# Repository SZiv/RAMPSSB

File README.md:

# RAMPSSB
=== Be sure to take a look at the Wiki before attempting a build: http://reprap.org/wiki/RAMPSSB and if you are curious more as to the development and technological reasoning behind this project, take a look at my blog post at http://scottziv.com/rampssb-bringing-closed-loop-dc-motor-control-to-3d-printers/ ===

RAMPS Servo Board. Released under GPLv3.

Replaces the X and Y stepper drivers on a RAMPS CNC control board with two channel DC motor quadrature encoder control using cheap, common, easy to solder components. Compatable with almost any 0-24V DC motor with a quadrature encoder that uses hall effect, optical, or mechanical rotary encoders. 

Uses a square L298N DC motor driver, attached with standoffs to the PCB, over 2 Arduino Pro Micros for control. PCB board is less than 100m square, so it can be produced for $5 + shipping from Seeedstudio, and the L298N driver board is cheap (like $3), and the controllers, Pro Micros, are maybe 5 bucks a piece.

For more steppers, this is compatable with the Reprap.me stepper expander, or, with some modification, my other board, the RAMPSXB. 

Can also be used as a simple non-RAMPS step/direction to DC encoder motor setup by directly wiring the pins. 

The firmware could use some work, and I am slowly developing it. It does function, but it is not as stable as I would like. If anyone has better luck with control software, let me know and I can add it to the official repo.

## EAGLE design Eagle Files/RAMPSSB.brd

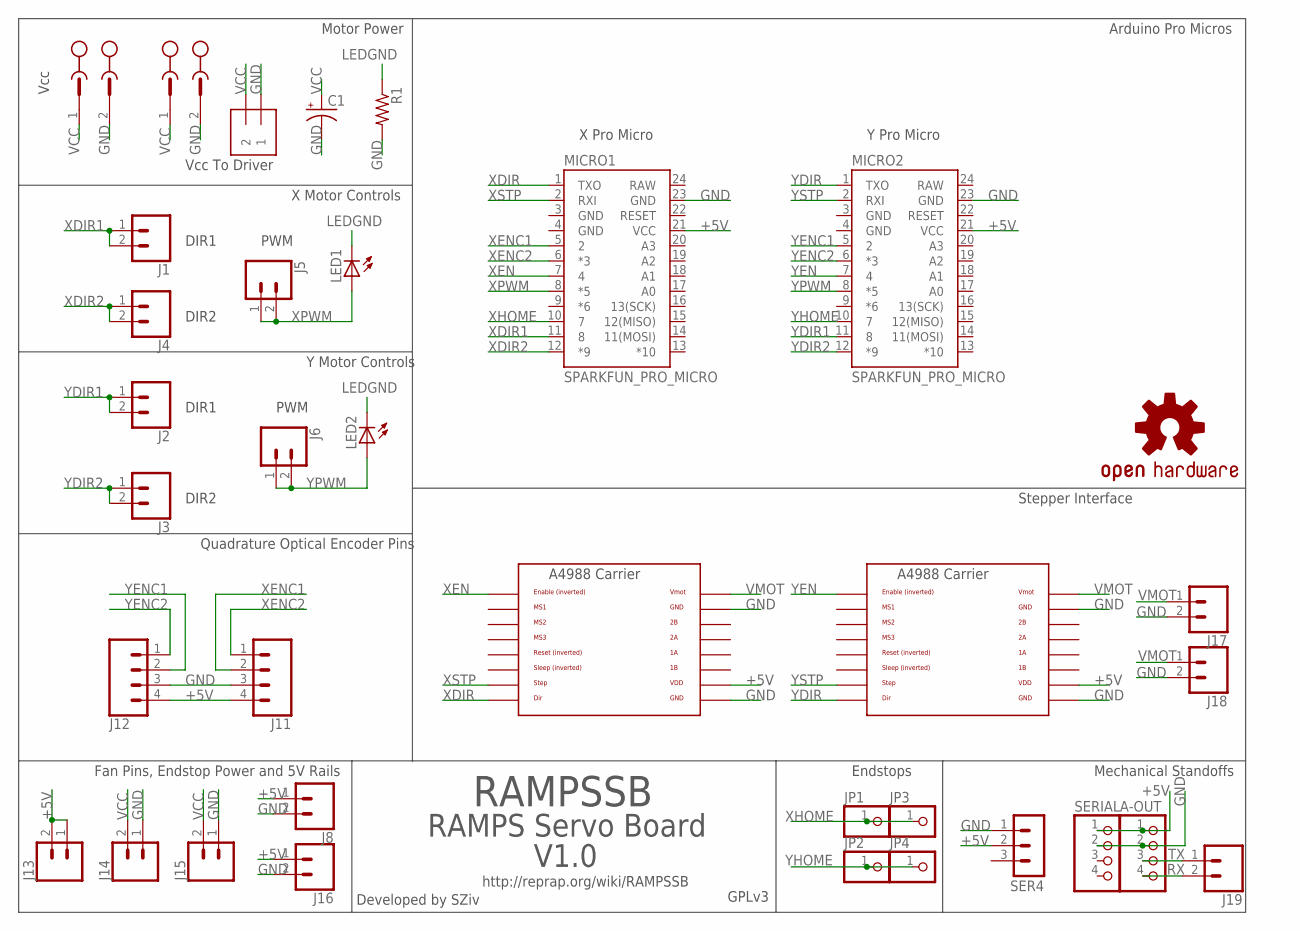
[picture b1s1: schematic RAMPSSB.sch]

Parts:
A-OUT: PINHD-1X4; 1X04
C1: CPOL-USE2.5-6; E2,5-6
J1, J2, J3, J4, J5, J6, J8, J13, J14, J15, J16, J17, J18, J19: CONN_02; 1X02
J7, J9: OSTTH020160; EDSTL130-02
J10: 1X2-3.5MM
J11, J12: CONN_04; 1X04
JP1, JP2, JP3, JP4: PINHD-1X1; 1X01
LED1, LED2: LED3MM
LOGO1: OSHW-LOGOL; OSHW-LOGO-L
MICRO1, MICRO2: SPARKFUN_PRO_MICRO
R1: R-US_0207/7; 0207/7
SER4: 3PIN-HEADER
SERIAL: PINHD-1X4; 1X04
U$6, U$7: A4988BREAKOUT

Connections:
+5V: A-OUT.1, J8.1, J11.4, J12.4, J13.1, J13.2, J16.1, MICRO1.21 (VCC), MICRO2.21 (VCC), SER4.2, SERIAL.1, U$6.VDD, U$7.VDD
GND: A-OUT.2, C1.-, J7.2, J8.2, J9.2, J10.1, J11.3, J12.3, J14.1, J15.1, J16.2, J17.2, J18.2, MICRO1.3 (GND), MICRO1.4 (GND), MICRO1.23 (GND), MICRO2.3 (GND), MICRO2.4 (GND), MICRO2.23 (GND), R1.2, SER4.1, SERIAL.2, U$6.GND, U$6.GND@0 (GND), U$7.GND, U$7.GND@0 (GND)
LEDGND: LED1.K (C), LED2.K (C), R1.1
RAW: MICRO1.24 (RAW), MICRO2.24 (RAW)
RX: A-OUT.4, J19.2
TX: A-OUT.3, J19.1
VCC: C1.+, J7.1, J9.1, J10.2, J14.2, J15.2
VMOT: J17.1, J18.1, U$6.VMOT, U$7.VMOT
XDIR: MICRO1.1 (TXO), U$6.DIR
XDIR1: J1.1, J1.2, MICRO1.11 (8)
XDIR2: J4.1, J4.2, MICRO1.12 (*9)
XEN: MICRO1.7 (4), U$6.EN
XENC1: J11.2, MICRO1.5 (2)
XENC2: J11.1, MICRO1.6 (*3)
XHOME: JP1.1, JP3.1, MICRO1.10 (7)
XPWM: J5.1, J5.2, LED1.A, MICRO1.8 (*5)
XSTP: MICRO1.2 (RXI), U$6.STEP
YDIR: MICRO2.1 (TXO), U$7.DIR
YDIR1: J2.1, J2.2, MICRO2.11 (8)
YDIR2: J3.1, J3.2, MICRO2.12 (*9)
YEN: MICRO2.7 (4), U$7.EN
YENC1: J12.2, MICRO2.5 (2)
YENC2: J12.1, MICRO2.6 (*3)
YHOME: JP2.1, JP4.1, MICRO2.10 (7)
YPWM: J6.1, J6.2, LED2.A, MICRO2.8 (*5)
YSTP: MICRO2.2 (RXI), U$7.STEP

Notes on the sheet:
DIR1
DIR2
PWM
Vcc To Driver
Vcc
Motor Power
X Motor Controls
Y Motor Controls
Quadrature Optical Encoder Pins
Fan Pins, Endstop Power and 5V Rails
Mechanical Standoffs
Stepper Interface
Arduino Pro Micros
RAMPSSB
RAMPS Servo Board
V1.0
Developed by SZiv
GPLv3
http://reprap.org/wiki/RAMPSSB
Endstops
X Pro Micro
Y Pro Micro

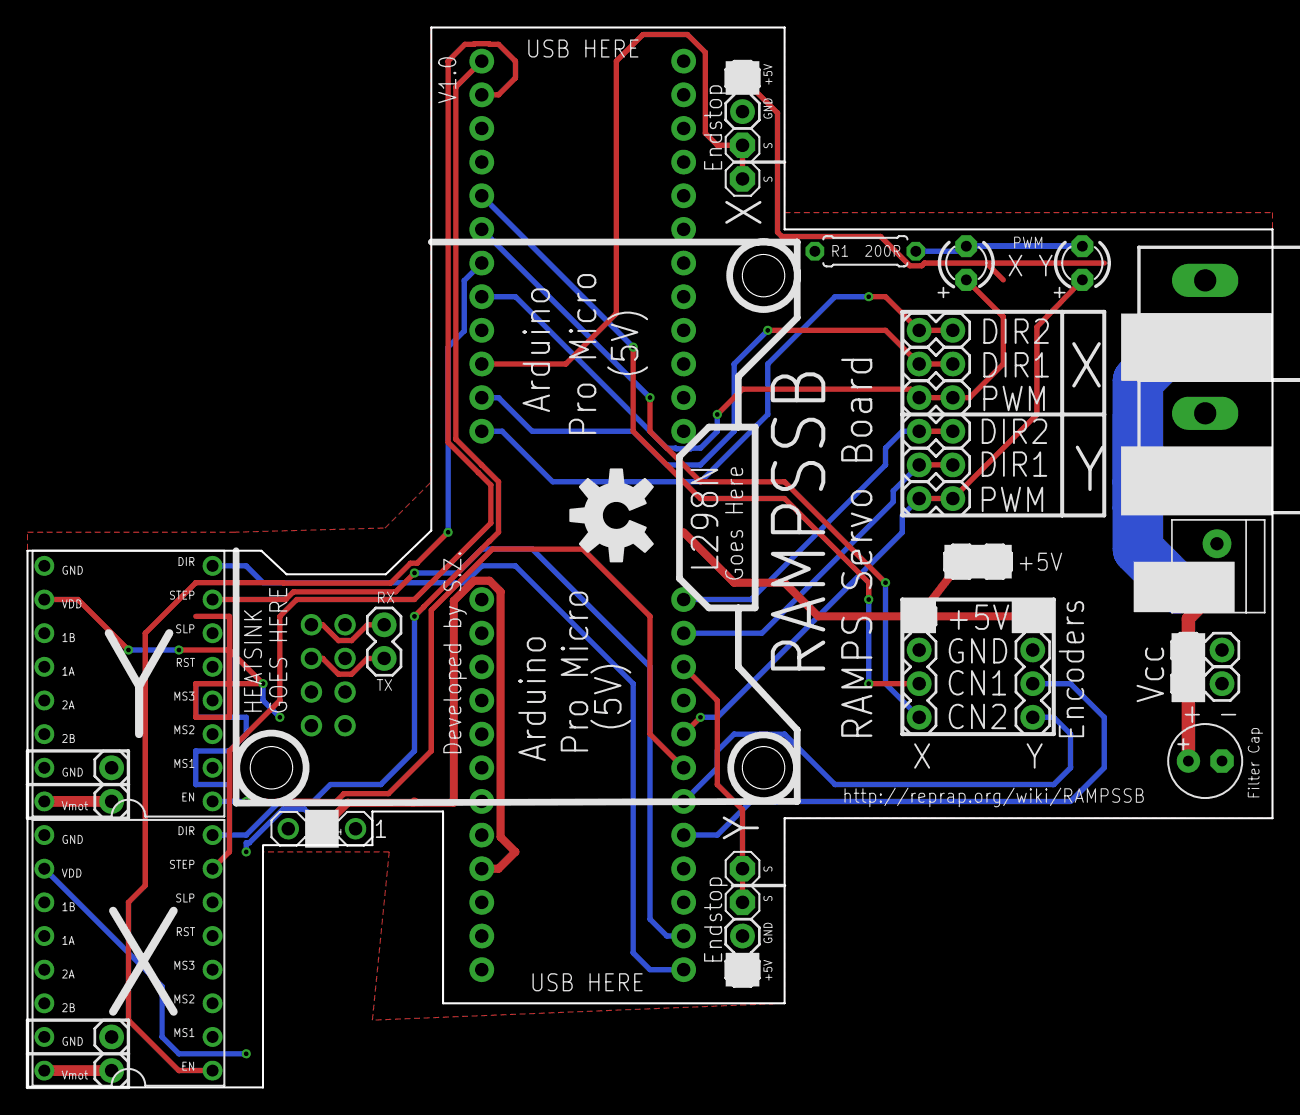
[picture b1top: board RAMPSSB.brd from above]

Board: 2 copper layers, 94.0 x 80.0 mm, 35 parts (0 on the bottom side), 26 nets.

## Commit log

2017-09-23 :space_invader: Added .gitattributes & .gitignore files
2017-09-23 Main Commit
    First Commit. Still waiting on board to test, and I have yet to write
    the software, but its up here if anyone wants to work with it.
    I havent written the Wiki page yet, but once I get a working version,
    I'll throw it up.
2017-10-13 Update for publish
    Final update before publish! Get ready!
    Still needs some firmware work, but the hardware is there.
2017-10-13 Firmware Adjustment
2017-10-19 Updated firmware to run Arduino-GPIO to increase speed of digital writes
2017-10-19 renamed PID_input to Error
    Renamed "PID_Input" to "Error" which is more realistic
2017-10-26 added blog post

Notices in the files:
parts and their libraries:
SparkFun-Retired: Licensing: Creative Commons ShareAlike 4.0 International - https://creativecommons.org/licenses/by-sa/4.0
con-ost: Copyright (C) 2008, Bob Starr
